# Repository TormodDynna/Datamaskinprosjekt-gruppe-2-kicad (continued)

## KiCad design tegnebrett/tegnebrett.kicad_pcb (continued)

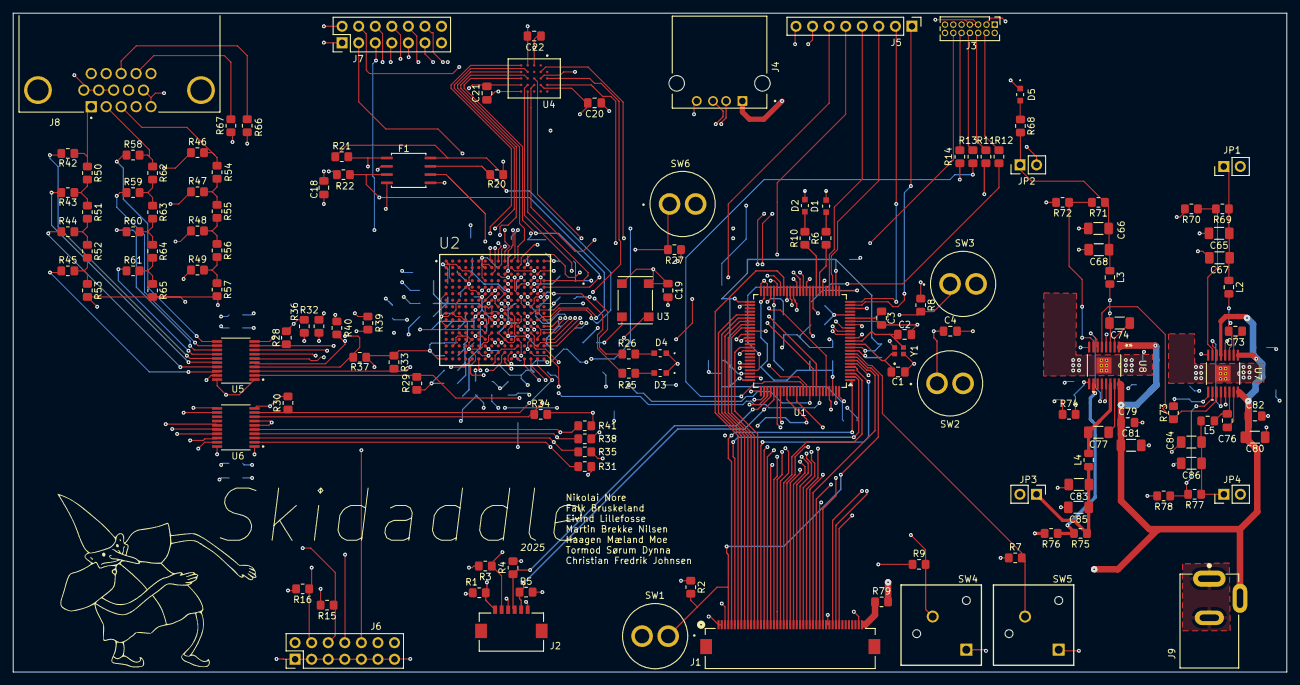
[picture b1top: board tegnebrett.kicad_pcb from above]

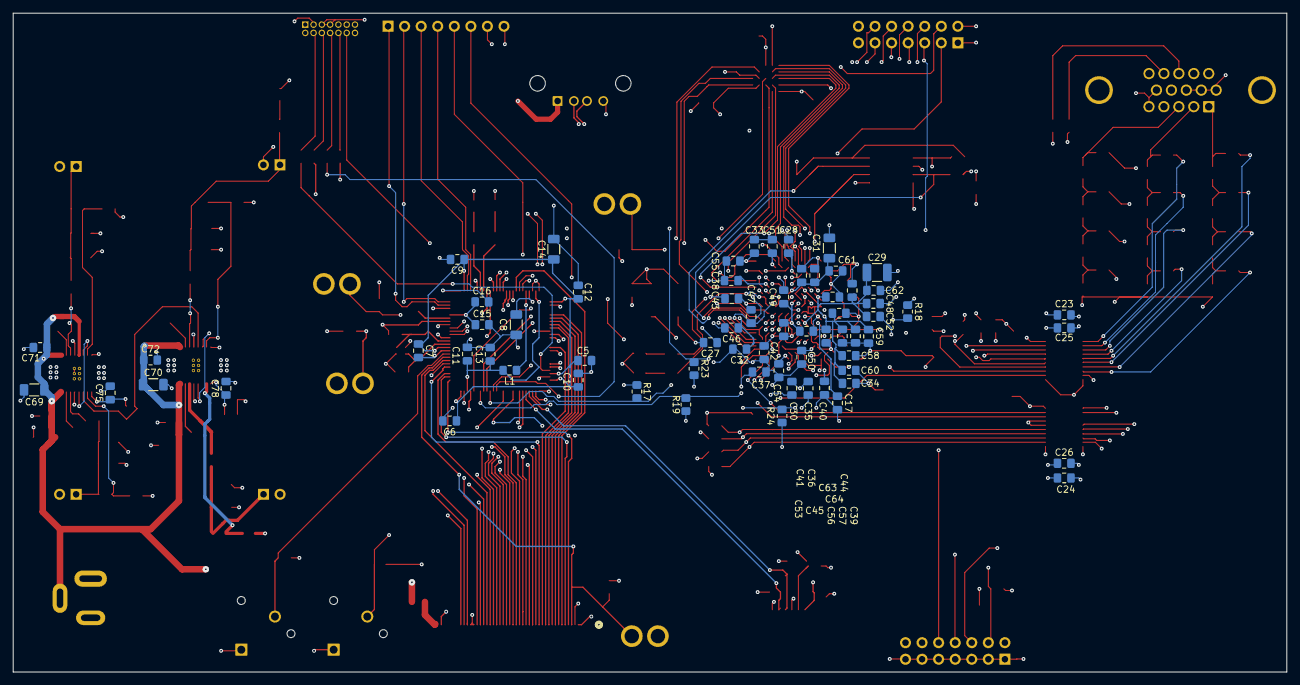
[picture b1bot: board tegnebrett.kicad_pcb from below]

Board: 6 copper layers, 195.2 x 101.0 mm, 204 parts (67 on the bottom side), 184 nets.

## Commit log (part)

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2025-09-24 feat: PCB update
    Main additions:
    - Added LEDs to Power Supply, MCU and FPGA.
    The resistor values will depend on the specific LEDs we buy.
    Red LEDs need a different resistor value than blue LEDs, etc.
    - Added a bunch of buttons to the MCU
    It doesn't hurt to have some redundancy here.
2025-09-24 feat: add Handleliste
    This is a start, where the shopping list has the main components for the
    MCU. We also need to buy a debug pin thing, and probably a connector
    which goes into the debug pin header.
    We also need a USB-A port.
    At a later stage we need to include all the FPGA-related components and
    the power supply.
2025-09-25 feat(PCB-schematic): add power flags
    This removes a lot of the warnings we're getting from the ERC checker.
    There are still some warnings on the PSU, probably because we've set the
    wrong pin type on some of the pins.
    For example output instead of power output, etc.
2025-09-25 feat: add 3D_models folder for custom modules
    I've currently put the connector 3D models in.
    The 3D model of the MCU is built into KiCAD.
2025-09-25 feat: added PCB file
    Placed the 45-pin connector and connected the 3D_model for it to the
    footprint.
2025-09-25 feat: add usb-A symbol, footprint and 3D model
2025-09-25 feat: add some footprints
    Added footprints to vertical 8pin connectors and so forth.
2025-09-26 feat: add USB-A symbol and footprint to schematic
    Also included the 3D model. Now there's some stuff in the PCB.
2025-09-26 feat: add 3d-models to custom footprints
    6pin and 45pin, USB-A.
2025-09-26 feat: remove old power supply schmatic
2025-09-26 docs: Tasks for Christian
2025-09-26 feat: add resistors between MCU debug and MCU
    These resistors are there in the slides from Asbjørn, so I assume they
    should be there. Couldn't find any information on series resistors to
    the debug pins in the data sheet. So they may or may not be actually
    needed.
2025-09-27 feat: add 100MHz oscillator footprint
    Additionally add the footprint to PCB.
2025-09-27 feat: add VGA Transceiver footprint
    Additionally add VGA Transceiver to PCB layout.
2025-09-27 feat: add psram footprint and add to PCB
2025-09-27 feat: add FPGA footprint and add footprint to PCB
2025-09-27 .gitignore: add libreoffice calc lock to gitignore
2025-09-27 feat: add LED footprint, and add them to PCB
2025-09-27 feat: add 48MHz crystal footprint + add to PCB
2025-09-27 docs: Add information on capacitors and their footprints
2025-09-27 feat: add footprint for each capacitor
    It's all 0805, 1206 or 1210 hand soldering variants.
2025-09-27 feat: add footprints to inductors
2025-09-27 docs: Add note on the different resistors and where to buy
2025-09-27 feat: add footprint to resistors
2025-09-28 refactor: remove some general bottuns from MCU
    We have gone down from 9 buttons total to 6 buttons total.
    One button is connected to the FPGA.
2025-09-28 feat: add footprint to FPGA_debug
2025-09-28 feat: add and import footprints of trash buttons
    These buttons are cheap and do the job fine.
2025-09-28 refactor: remove unused LEDs
    We have too many LEDs.
    We're thinking two LEDs for the MCU and two LEDs for the FPGA.
    Additionally have one Green LED at power supply to indicate that power
    is on.
2025-09-28 refactor: use new LED variants.
    These have a supply voltage of 2V, and they have a current of 5mA.
    These are nice numbers which gives a required resistance of 260 Ohm,
    assuming a supply voltage of 3.3V
    We're using 270 Ohms though, as 260 is not standard.
2025-09-28 feat: add LED to 3.3V from power supply, and set resistors to 270ohm.
    Additionally add footprints to these resistors which *did not* yet have
    a footprint (because their resistor values were not determined yet).
2025-09-28 feat: add 15V power jack symbol and import to schematic
2025-09-28 feat: sort components on PCB layout.
    Done by Tormod Sørum Dynna
2025-09-28 feat: add jumpers to PowerSupply schematic
2025-09-28 feat: add footprint to jumper and import to PCB
2025-09-29 pcb: update from schematic
    reloads the annotations used.
2025-09-29 refactor: make FPGA_Header_Pin 2x7 instead of 1x8
    We'll get some more GPIO pins exposed.
2025-09-29 gitignore: Ignore backup files (.bak)
2025-09-29 feat: add power_down_transformator symbol
    I've moved this symbol to the *tegnebrett_symbols* file.
    Apparently it is the case that multiple symbols are stored within one
    .kicad_sym file.
    I **also** moved the PJ (Power Jack) symbol to this file.
    Preparing to remove the PJ symbol file, and also the symbols folder.
    Everything is stored in the (misnamed) USB....kicad_sym file.
2025-09-29 refactor: update power-down-transformer symbol
    Update pin functions and so forth.
2025-09-29 feat: update symbol for second power down transformer
    Somehow I had managed to update one symbol, not both (the parts are
    identical).
2025-09-29 refactor: rename debuc.kicad_sch into FPGA.kicad_sch
    Easier to reason about. Also updated the main sheet such that it refers
    to this new filename.
2025-09-29 refactor: rename power supply file
    Additionally remove older unused schematics which were present in the
    *tegnebrett* folder.
2025-09-29 refactor: rename project from getting-started to tegnebrett
2025-09-29 rename: VGA1.kicad_sch got renamed into VGA
    It's confusing to have VGA1 when we only have one VGA schematic sheet.
2025-09-29 feat: add custom oscillator symbol
    We're ending up not using it, because *passive* is actually correct pin
    classification, even if the ERC gives errors when we have it on.
2025-09-29 misc: internal updates in schematic files
    project name is being updated from *getting-started* to *tegnebrett*
2025-09-29 fix: add PWR_FLAG symbol to Power supply schematic
    This reduces errors, now we only have one error left.
2025-09-29 superfeat: PCB updates from Tormod
2025-09-29 fix: Fix error saying that Ground pin isn't powered by power source.
    Did this by adding a PWR_FLAG to the schematic.
2025-09-29 fix: remove unused cable
    This removes one warning.
    The cable was connected in one end, unconnected in the other.
    Had no purpose at all.
2025-09-29 fix: add FPGA debug symbol to tegnebrett_symbols library
    This was a symbol added by Tormod which has also been lost to time.
    No problems, we just save the symbol into *tegnebrett_symbols*.
    I believe we will change the pin functions as well.
2025-09-29 refactor: move SCK_FPGA from N11 to N14
    This allows for easier routing on the PCB.
2025-09-29 fix: add FPGA Oscillator 100MHz to tegnebrett_symbols file
    This is one symbol which Tormod created locally which got lost to time.
2025-09-29 fix: remove unused labels in FPGA.kicad_sch
    Two labels which were only defined once (no matching label) were
    removed.
    Result: Two less warnings in the ERC checker. Now only 30 warnings.
2025-09-29 fix: add separate symbols for larger switches.
    They need pin1 and pin3, not pin1 and pin2.
    The PCB editor throws an error when pin3 is not present on the button
    symbol.
2025-09-29 refactor: move FPGA button from g12 to a13 pin on FPGA
    g12 -> a13
    This makes the routing easier.
2025-09-30 gitignore: Remove .kicac_prl from index and add to gitignore
    This is a file which only holds user-specific config on how symbols
    should be displayed, etc.
2025-09-30 chore: remove todo-christian.md
    All the tasks have been done, no need for it remain in root folder.
2025-09-30 feat: update Handleliste.xlsx
    Include information on crystal, oscillator, down transformer and FPGA
    flash.
    Additionally included the names of all the parts (except capacitors,
    resistors, buttons, etc.) which I still haven't found the link to.
2025-09-30 chore: move silkprint in PWP16 module
    More changes are coming to this footprint soon, there's some mismatch
    between symbol and footprint.
2025-09-30 docs: add FPGA, VGA-port and SRAM to shopping list
    Oscillator got updated, the initial entry was wrong.
2025-09-30 feat: update PCB
    Pulled the latest changes from Tormod and imported the EPAD -> 17 fix.
    Still, there are some warnings telling us that some footprints have pins
    which are not present on the symbols.
2025-09-30 feat: add skidaddle-logo silkscreen
    Did some image editing in GIMP before getting the size and so forth
    correct.
2025-09-30 fix: remove unused circuit label
    Removes one warning.
    Total warning count is now 20.
2025-09-30 fix: Add separate symbol for second VGA-transceiver
    Some pins are bi-directional on the one symbol, but grounded on the
    other. This new symbol and subsequent update to schematic symbol reduces
    the warning count by 2.
2025-09-30 fix: add project-local variant of FPGA symbol
    Allows us to set some bi-directional pins to *power input*, as some of
    the bi-directionals are connected to GND and VDD. KiCAD threw warning
    because of that.
    Now the warning count is down to 1.
2025-09-30 fix: remove unused net labels in main MCU sheet
    I had used labels called *VDD_W_DECOUPLING* and so forth, but these were
    identical in nature to +3V3. The chatbot is saying that we ideally
    should have different subnets (whatever that means). Would be necessary
    in larger projects, but it's fine to have just +3V3 in this small
    schematic/PCB layout.
    This removed the last warning in the ERC checker for the schematic.
2025-09-30 feat: PCB updates
    Latest stuff from Tormod.
    We still have 77 Errors and 2 warnings, but we'll ship this!
2025-09-30 chore: Remove .txt files
    These were used to get a quick overview of our inductors, capacitors and
    resistors. The data has been moved into the excel sheet, so we don't
    need the .txt files anymore.
2025-09-30 feat: add remaining components and prices to Handleliste
    We've now got all (probably) hardware stuff in the shopping list.
    The total price lies at 9909 NOK.
    Should probably check that we've actually included all components, but
    there's a good chance we actually do have them all.
2025-10-01 fix: Edit footprint such that vias have pin number 17
    This allows KiCAD to understand that the pad and the thermal vias are
    connected to the same layer (GND). It reduces the errors we get from DRC
    in PCB layout from 72 to 10.
2025-10-01 fix: change *zone connection style* for thermal vias
    Change from *inherited* to *solid*.
    This means that there are no longer any *copper spokes* going from the
    thermal vias to the rest of the thermal pad (which also has pin number
    17).
    This *increases* thermal conductivity, but makes it somewhat *harder* to
    solder the chip onto the PCB when we're doing hand-soldering.
2025-10-01 chore: update power transformers in PCB layout
    Completes the transition to *solid* zone connection style for thermal
    vias.
2025-10-04 feat: PCB updates
    Latest changes from Tormod. Fixed warnings and errors.
    Additionally moved the LCD screen connector ports to better fit the
    actual LCD screen.
2025-10-04 fix: change layers to get correct impedance
    GND is now on layer2, the USB-A stuff needs correct impedance.
2025-10-04 fix: import LCD resistor to PCB
    Again, this is to limit the current going through the LCD screen.
2025-10-04 fix: update FPGA flash footprint
    Now the front silkscreen no longer goes over the holes in the front
    mask.
2025-10-04 fix: move LCD screen 6-pin connector to better position
    1 mm right and 3 mm up into the PCB.
2025-10-04 docs: latest version of Handleliste-hardware
2025-10-28 feat: add .svg version of logo
    We're going to have this on our T-shirts at the presentation.
2025-11-18 docs: add system overview draw.io file
    When opened in draw.io, you'll see a quick overview of the main
    components on the PCB, and the communication interfaces which exist
    between the components.
